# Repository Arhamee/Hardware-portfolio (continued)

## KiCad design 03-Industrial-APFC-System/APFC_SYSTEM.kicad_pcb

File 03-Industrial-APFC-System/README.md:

# Industrial Automatic Power Factor Correction System

Single-phase APFC system for loads up to 5kW, designed for real industrial
deployment in a DIN rail enclosure.

**Status:** In progress · 4-layer layout · to be open-sourced on OSHWLab
(OSHWLab Stars 2026)

## The Problem
Inductive loads — motors, compressors, welding machines — draw reactive current
that inflates bills and stresses wiring without doing useful work. Most affordable
solutions only *monitor*. This one corrects.

## Hardware
| Block | Part / Approach |
|---|---|
| MCU | ESP32-WROOM-32E (dual core, WiFi) |
| Voltage sensing | Isolated, via potential transformer |
| Current sensing | SCT-013 split-core CT (galvanic isolation) |
| Capacitor bank | Binary-weighted 60/120/240µF CBB65 — 7 steps, 1–7 kVAR |
| Switching | S216S02 solid state relays, zero-cross |
| Protection | MOV surge clamping · DIN rail EMI filter · fused mains · TVS |
| Display | SH1106 OLED |

## PCB
4-layer mixed-signal design:
- Mains-side isolated on bottom layer
- Analog sensing shielded by ground plane
- DIN rail form factor for direct panel installation

## Firmware / Dashboard
Live WiFi dashboard (no internet required) reporting Vrms, Irms, active/reactive/
apparent power, power factor, and capacitor bank status.

## Prior Version
Started as a Veroboard build with an Arduino Nano — calibrated sensors,
relay-switched capacitor bank, hysteresis-based correction algorithm.

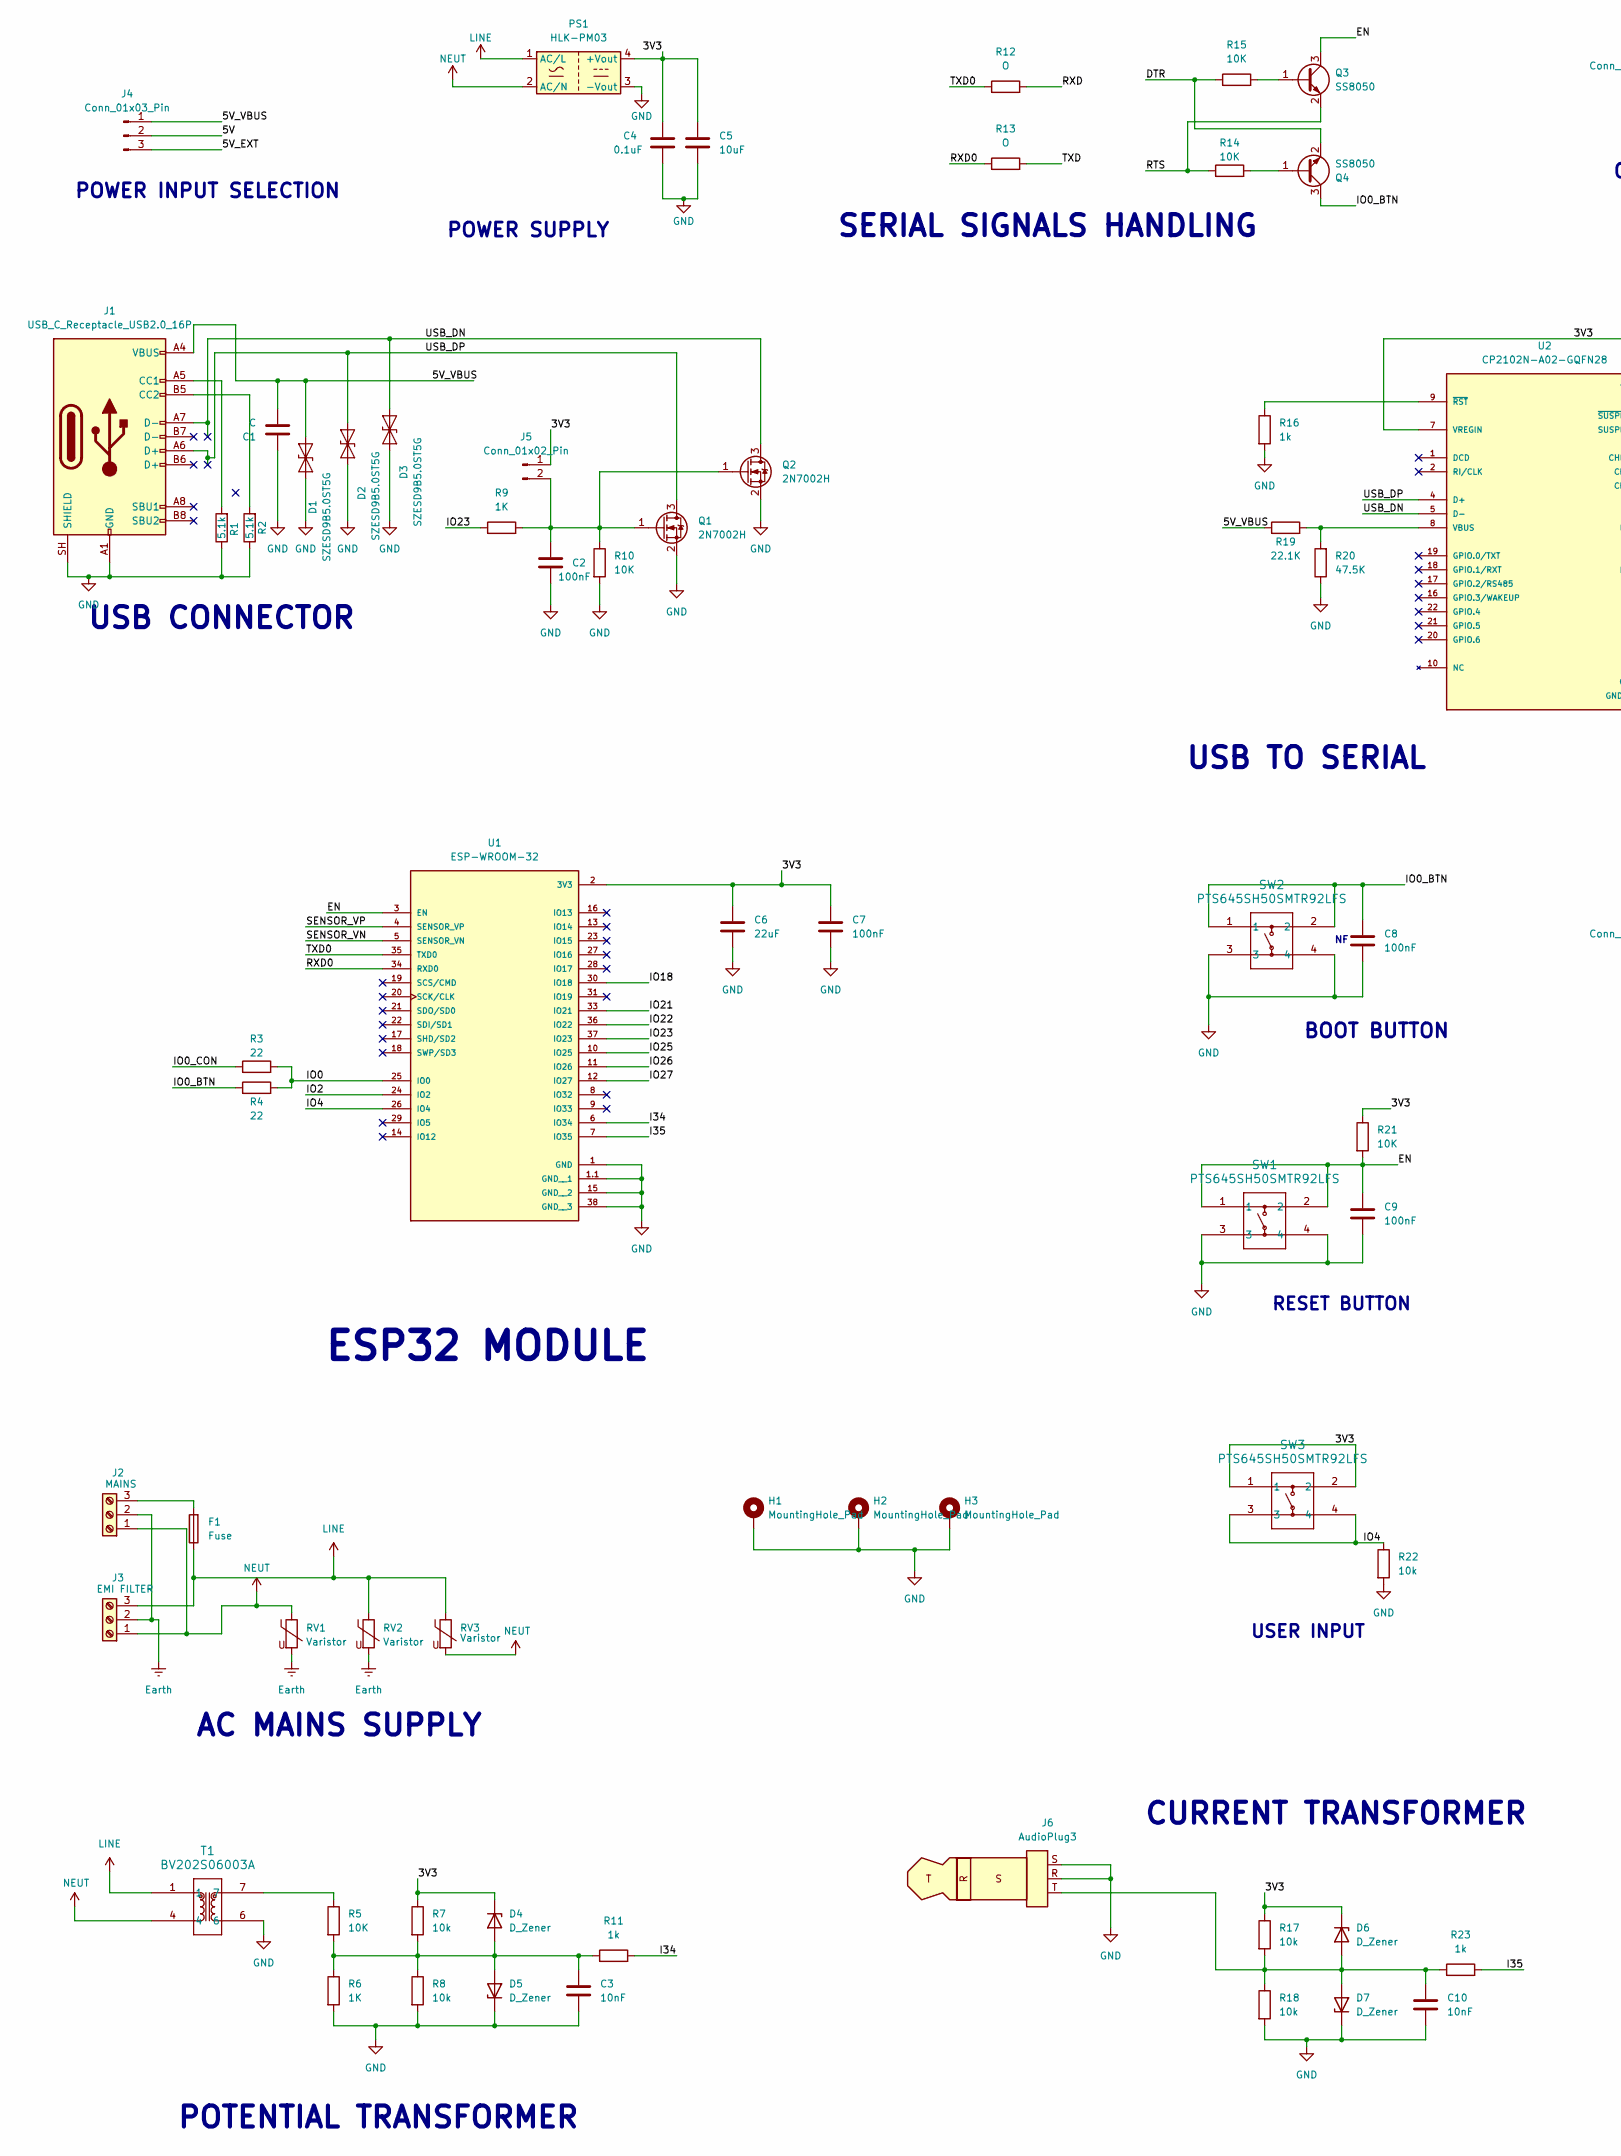
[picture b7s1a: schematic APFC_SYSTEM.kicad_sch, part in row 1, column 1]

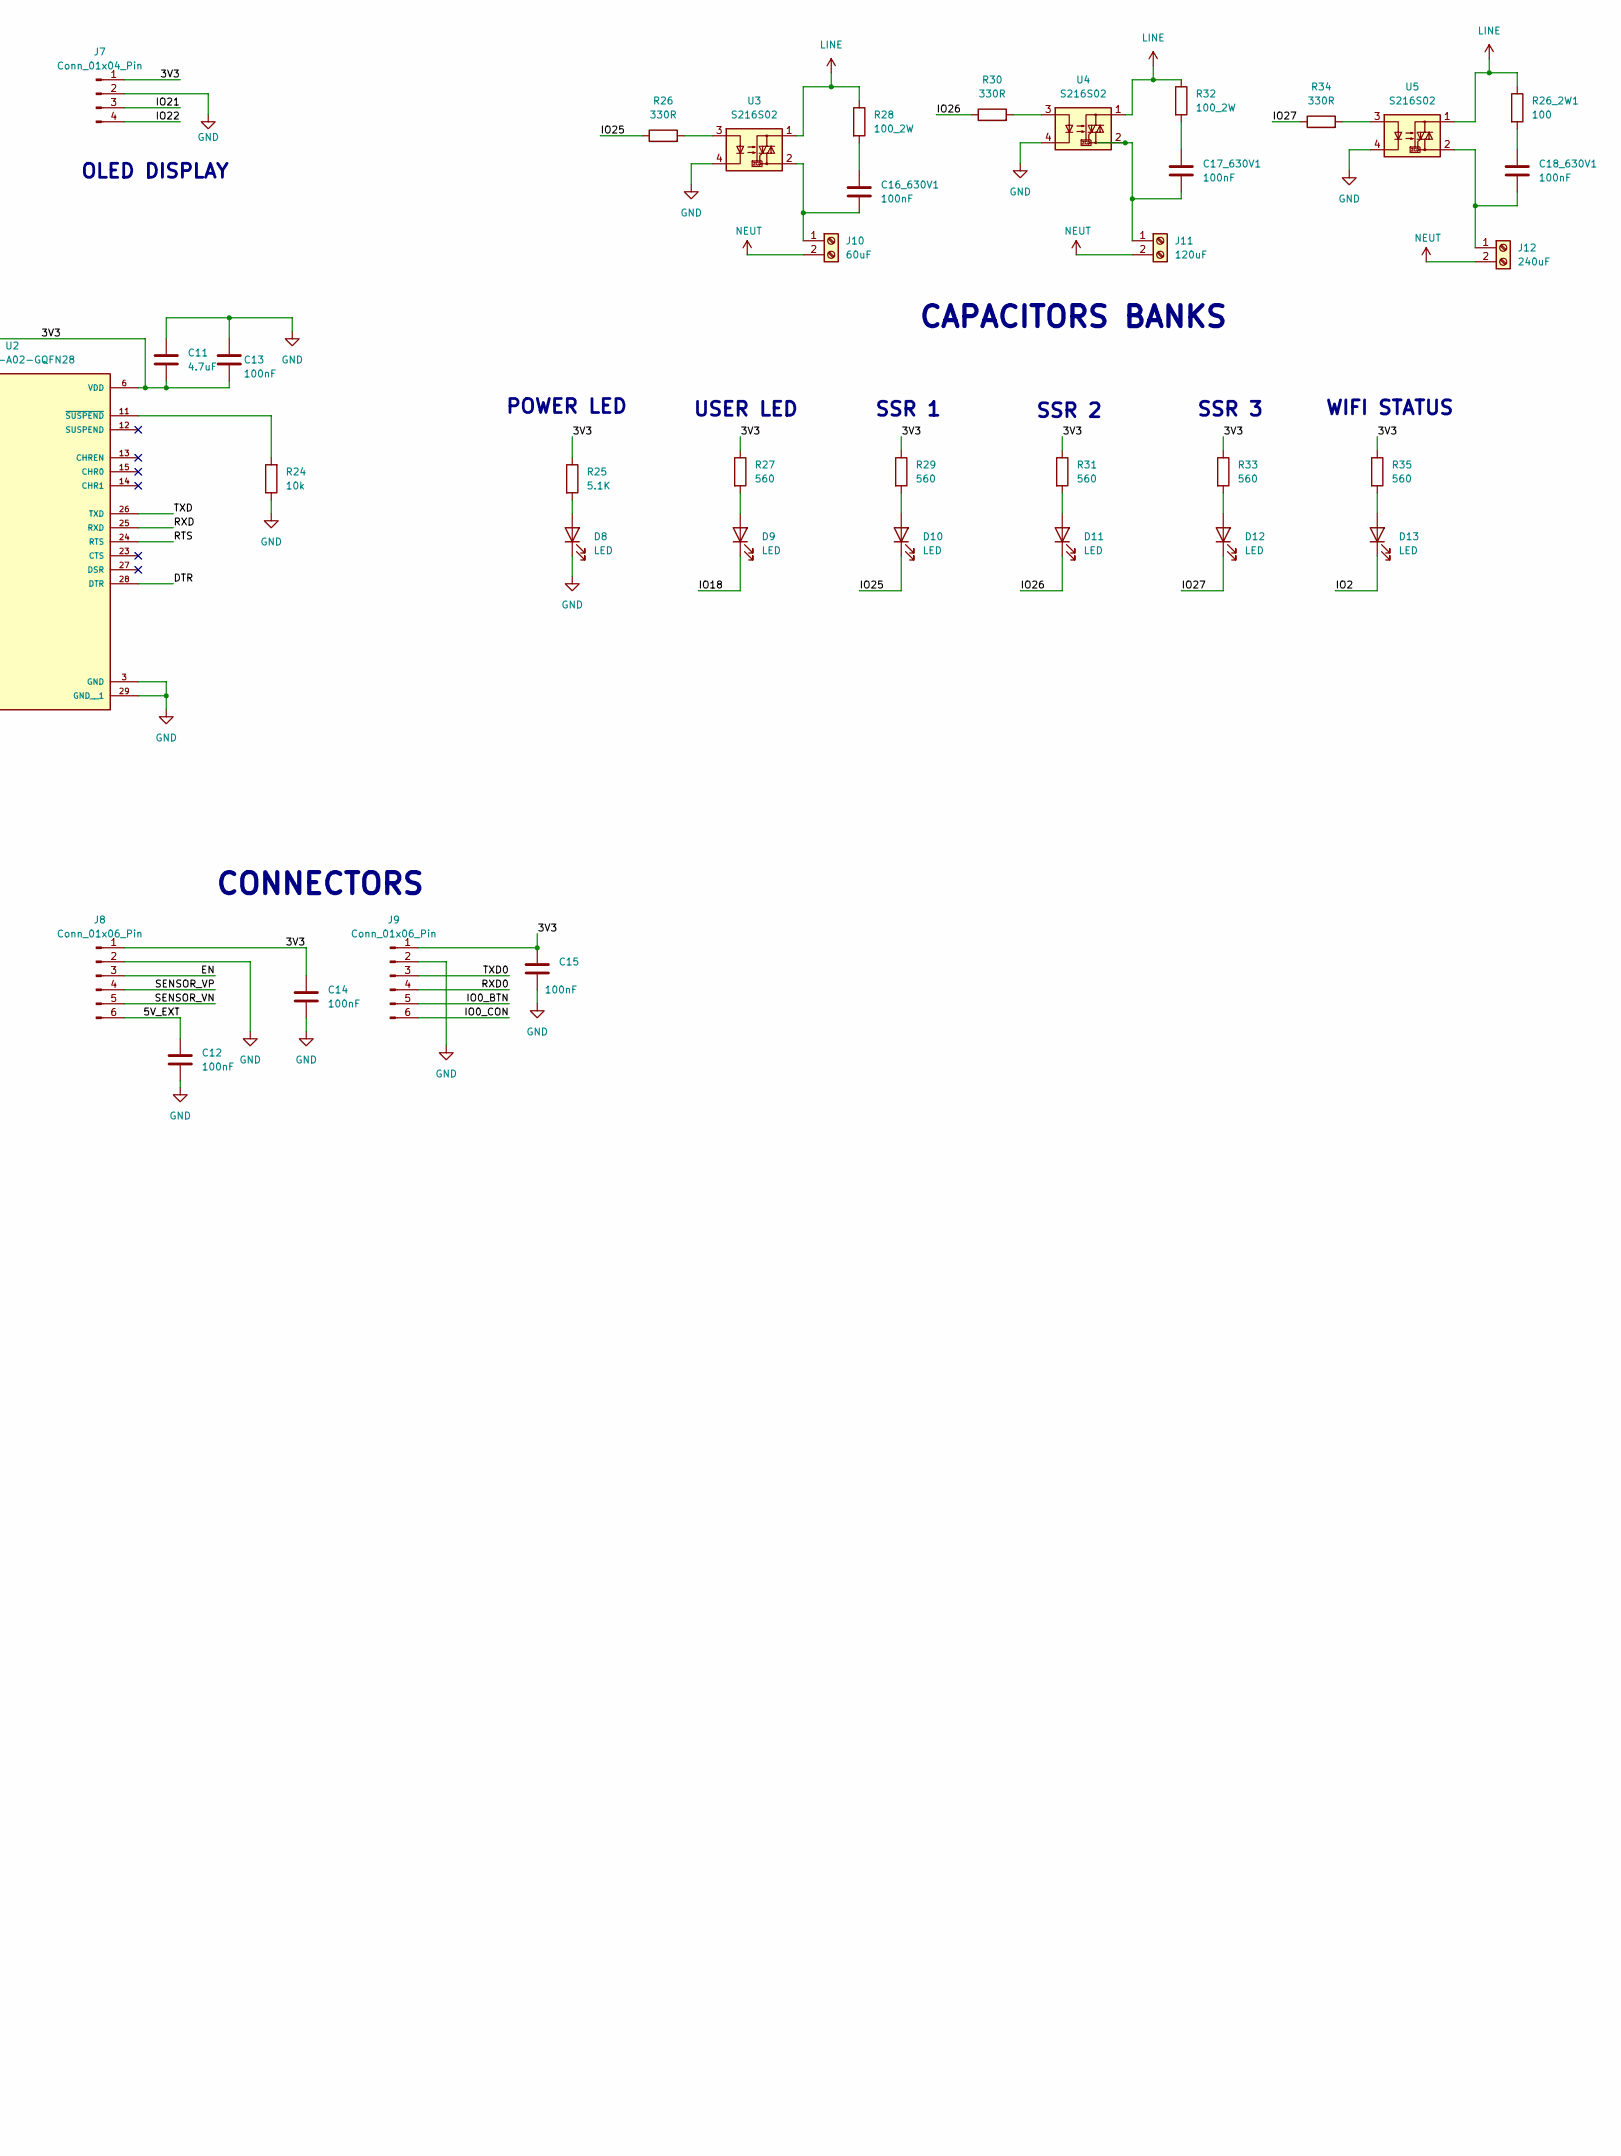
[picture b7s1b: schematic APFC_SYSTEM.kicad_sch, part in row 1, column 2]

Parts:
C1: C; C_0603_1608Metric_Pad1.08x0.95mm_HandSolder
C2, C7, C8, C9, C12, C13, C14, C15: 100nF; C_0603_1608Metric_Pad1.08x0.95mm_HandSolder
C3, C10: 10nF; C_0603_1608Metric_Pad1.08x0.95mm_HandSolder
C4: 0.1uF; C_0603_1608Metric_Pad1.08x0.95mm_HandSolder
C5: 10uF; C_0805_2012Metric_Pad1.18x1.45mm_HandSolder
C6: 22uF; C_0805_2012Metric_Pad1.18x1.45mm_HandSolder
C11: 4.7uF; C_0805_2012Metric_Pad1.18x1.45mm_HandSolder
C16_630V1, C17_630V1, C18_630V1: 100nF; C_Disc_D7.5mm_W5.0mm_P10.00mm
D1, D2, D3: SZESD9B5.0ST5G; D_SOD-923
D4, D5, D6, D7: D_Zener; D_0805_2012Metric_Pad1.15x1.40mm_HandSolder
D8, D9, D10, D11, D12, D13: LED; LED_0603_1608Metric_Pad1.05x0.95mm_HandSolder
F1: Fuse; FUSE_696105003002
H1, H2, H3: MountingHole_Pad; MountingHole_4.3mm_M4_DIN965_Pad
J1: USB_C_Receptacle_USB2.0_16P; USB_C_Receptacle_GCT_USB4105-xx-A_16P_TopMnt_Horizontal
J2: MAINS; TerminalBlock_Ningbo-Kagnex_HB9500M_1x03_P9.5mm
J3: EMI FILTER; TerminalBlock_Ningbo-Kagnex_HB9500M_1x03_P9.5mm
J4: Conn_01x03_Pin; PinHeader_1x03_P2.00mm_Vertical
J5: Conn_01x02_Pin; PinHeader_1x02_P1.27mm_Vertical
J6: AudioPlug3; Jack_3.5mm_CUI_SJ-3523-SMT_Horizontal
J7: Conn_01x04_Pin; PinHeader_1x04_P2.54mm_Vertical
J8, J9: Conn_01x06_Pin; PinHeader_1x06_P2.00mm_Vertical
J10: 60uF; TerminalBlock_Ningbo-Kagnex_HB9500M_1x02_P9.5mm
J11: 120uF; TerminalBlock_Ningbo-Kagnex_HB9500M_1x02_P9.5mm
J12: 240uF; TerminalBlock_Ningbo-Kagnex_HB9500M_1x02_P9.5mm
PS1: HLK-PM03; Converter_ACDC_Hi-Link_HLK-PMxx
Q1, Q2: 2N7002H; SOT-23
Q3, Q4: SS8050; SOT-23
R1, R2: 5.1k; R_0603_1608Metric_Pad0.98x0.95mm_HandSolder
R3, R4: 22; R_0402_1005Metric_Pad0.72x0.64mm_HandSolder
R5, R10, R14, R15: 10K; R_0603_1608Metric_Pad0.98x0.95mm_HandSolder
R6, R9: 1K; R_0603_1608Metric_Pad0.98x0.95mm_HandSolder
R7, R8, R17, R18, R22: 10k; R_0603_1608Metric_Pad0.98x0.95mm_HandSolder
R11, R23: 1k; R_0603_1608Metric_Pad0.98x0.95mm_HandSolder
R12, R13: O; R_0603_1608Metric_Pad0.98x0.95mm_HandSolder
R16: 1k; R_0402_1005Metric_Pad0.72x0.64mm_HandSolder
R19: 22.1K; R_0402_1005Metric_Pad0.72x0.64mm_HandSolder
R20: 47.5K; R_0402_1005Metric_Pad0.72x0.64mm_HandSolder
R21: 10K; R_0402_1005Metric_Pad0.72x0.64mm_HandSolder
R24: 10k; R_0402_1005Metric_Pad0.72x0.64mm_HandSolder
R25: 5.1K; R_0402_1005Metric_Pad0.72x0.64mm_HandSolder
R26, R30, R34: 330R; R_0603_1608Metric_Pad0.98x0.95mm_HandSolder
R26_2W1: 100; R_Axial_DIN0309_L9.0mm_D3.2mm_P15.24mm_Horizontal
R27: 560; R_0402_1005Metric_Pad0.72x0.64mm_HandSolder
R28, R32: 100_2W; R_Axial_DIN0309_L9.0mm_D3.2mm_P15.24mm_Horizontal
R29, R31, R33, R35: 560; R_0603_1608Metric_Pad0.98x0.95mm_HandSolder
RV1, RV2, RV3: Varistor; RV_Disc_D15.5mm_W3.9mm_P7.5mm
SW1, SW2, SW3: PTS645SH50SMTR92LFS; PTS645S_SMTR92_CNK
T1: BV202S06003A; VOLTAGE_TRANSFORMER
U1: ESP-WROOM-32; MODULE_ESP-WROOM-32
U2: CP2102N-A02-GQFN28; QFN50P500X500X80-29N; PARTREV 1.5
U3, U4, U5: S216S02; SIP4_Sharp-SSR_P7.62mm_Straight

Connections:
/3V3: C4.1, C5.1, C6.1, C7.1, C11.2, C13.2, C14.1, C15.1, D4.1 (K), D6.1 (K), J5.1, J7.1, J8.1, J9.1, PS1.4 (+Vout), R7.1, R17.1, R21.1, R25.1, R27.1, R29.1, R31.1, R33.1, R35.1, SW3.1, SW3.2, U1.2 (3V3), U2.6 (VDD), U2.7 (VREGIN)
/5V: J4.2
/5V_EXT: C12.1, J4.3, J8.6
/5V_VBUS: C1.2, D1.2 (A2), J1.A4 (VBUS), J1.A9 (VBUS), J1.B4 (VBUS), J1.B9 (VBUS), J4.1, R19.1
/DTR: Q4.2 (E), R15.1, U2.28 (DTR)
/EN: C9.1, J8.3, Q3.3 (C), R21.2, SW1.1, SW1.2, U1.3 (EN)
/I34: R11.2, U1.6 (IO34)
/I35: R23.2, U1.7 (IO35)
/IO0: R3.2, R4.2, U1.25 (IO0)
/IO0_BTN: C8.1, J9.5, Q4.3 (C), R4.1, SW2.1, SW2.2
/IO0_CON: J9.6, R3.1
/IO2: D13.1 (K), U1.24 (IO2)
/IO4: R22.1, SW3.3, SW3.4, U1.26 (IO4)
/IO18: D9.1 (K), U1.30 (IO18)
/IO21: J7.3, U1.33 (IO21)
/IO22: J7.4, U1.36 (IO22)
/IO23: R9.1, U1.37 (IO23)
/IO25: D10.1 (K), R26.1, U1.10 (IO25)
/IO26: D11.1 (K), R30.1, U1.11 (IO26)
/IO27: D12.1 (K), R34.1, U1.12 (IO27)
/RTS: Q3.2 (E), R14.1, U2.24 (RTS)
/RXD: R12.2, U2.25 (RXD)
/RXD0: J9.4, R13.1, U1.34 (RXD0)
/SENSOR_VN: J8.5, U1.5 (SENSOR_VN)
/SENSOR_VP: J8.4, U1.4 (SENSOR_VP)
/TXD: R13.2, U2.26 (TXD)
/TXD0: J9.3, R12.1, U1.35 (TXD0)
/USB_DN: D3.2 (A2), J1.A7 (D-), Q2.3 (D), U2.5 (D-)
/USB_DP: D2.2 (A2), J1.A6 (D+), Q1.3 (D), U2.4 (D+)
Earth: J2.2, J3.2, RV1.2, RV2.2
GND: C1.1, C2.2, C3.2, C4.2, C5.2, C6.2, C7.2, C8.2, C9.2, C10.2, C11.1, C12.2, C13.1, C14.2, C15.2, D1.1 (A1), D2.1 (A1), D3.1 (A1), D5.1 (K), D7.1 (K), D8.1 (K), H1.1 (1_1), H2.1 (1_1), H3.1 (1_1), J1.A1 (GND), J1.A12 (GND), J1.B1 (GND), J1.B12 (GND), J1.SH (SHIELD), J6.R, J6.S, J7.2, J8.2, J9.2, PS1.3 (-Vout), Q1.2 (S), Q2.2 (S), R1.1, R2.1, R6.2, R8.2, R10.2, R16.2, R18.2, R20.1, R22.2, R24.1, SW1.3, SW1.4, SW2.3, SW2.4, T1.6, U1.1 (GND), U1.1.1 (GND__1), U1.15 (GND__2), U1.38 (GND__3), U2.3 (GND), U2.29 (GND__1), U3.4, U4.4, U5.4
LINE: F1.1, J3.3, PS1.1 (AC/L), R26_2W1.1, R28.1, R32.1, RV2.1, RV3.1, T1.1, U3.1, U4.1, U5.1
NEUT: J2.1, J3.1, J10.2, J11.2, J12.2, PS1.2 (AC/N), RV1.1, RV3.2, T1.4
unnamed: C16_630V1.1, R28.2
unnamed: C17_630V1.1, R32.2
unnamed: C18_630V1.1, R26_2W1.2
unnamed: C3.1, D4.2 (A), D5.2 (A), R5.2, R6.1, R7.2, R8.1, R11.1
unnamed: C10.1, D6.2 (A), D7.2 (A), J6.T, R17.2, R18.1, R23.1
unnamed: D8.2 (A), R25.2
unnamed: D9.2 (A), R27.2
unnamed: D10.2 (A), R29.2
unnamed: D11.2 (A), R31.2
unnamed: D12.2 (A), R33.2
unnamed: D13.2 (A), R35.2
unnamed: J1.A5 (CC1), R1.2
unnamed: J1.B5 (CC2), R2.2
unnamed: F1.2, J2.3
unnamed: C2.1, J5.2, Q1.1 (G), Q2.1 (G), R9.2, R10.1
unnamed: C16_630V1.2, J10.1, U3.2
unnamed: C17_630V1.2, J11.1, U4.2
unnamed: C18_630V1.2, J12.1, U5.2
unnamed: Q3.1 (B), R15.2
unnamed: Q4.1 (B), R14.2
unnamed: R5.1, T1.7
unnamed: R26.2, U3.3
unnamed: R30.2, U4.3
unnamed: R34.2, U5.3
unnamed: R19.2, R20.2, U2.8 (VBUS)
unnamed: R16.1, U2.9 (~RST)
unnamed: R24.2, U2.11 (~SUSPEND)

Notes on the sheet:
CURRENT TRANSFORMER
CAPACITORS BANKS
WIFI STATUS
SERIAL SIGNALS HANDLING
SSR 1
POWER LED
POTENTIAL TRANSFORMER
POWER INPUT SELECTION
USB CONNECTOR
USER LED
CONNECTORS
SSR 2
AC MAINS SUPPLY
BOOT BUTTON
USB TO SERIAL
OLED DISPLAY
RESET BUTTON
ESP32 MODULE
SSR 3
USER INPUT
POWER SUPPLY

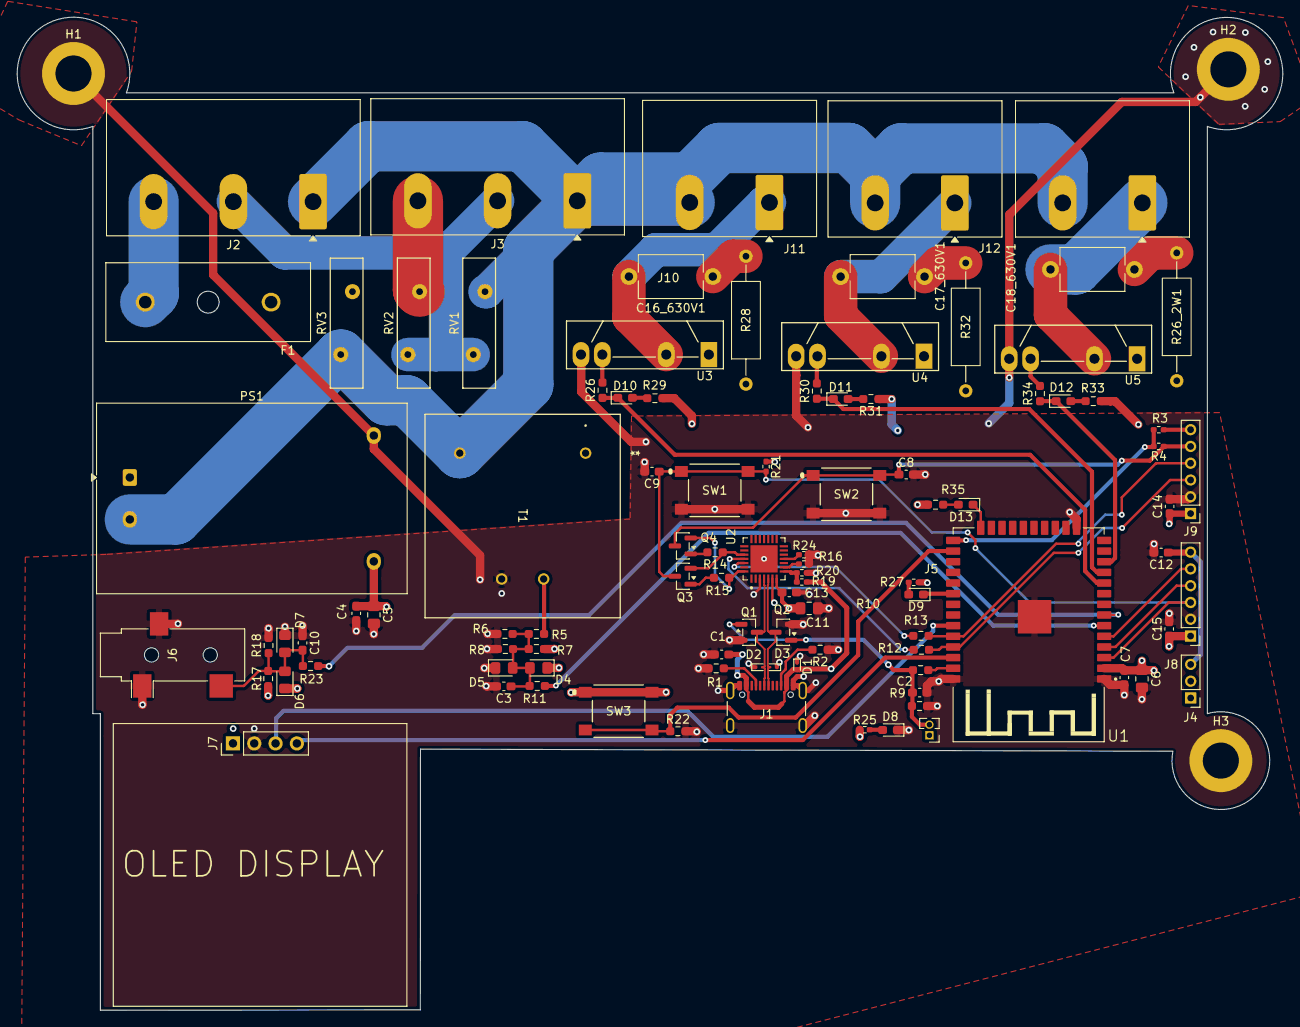
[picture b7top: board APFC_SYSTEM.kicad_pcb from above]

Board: 4 copper layers, 150.9 x 118.4 mm, 100 parts (0 on the bottom side), 59 nets.

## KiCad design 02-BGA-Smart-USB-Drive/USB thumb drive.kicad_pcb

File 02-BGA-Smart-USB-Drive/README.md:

# Smart USB Thumb Drive — RP2040 + eMMC

4-layer board packing an RP2040, USB2244 bridge, and 64GB eMMC in a
153-ball 0.5mm-pitch BGA into a thumb-drive footprint.

**Status:** Design complete · DRC-clean · manufacturing-ready · not yet fabricated

## Specs
| | |
|---|---|
| Layers | 4 |
| MCU | RP2040 |
| Bridge | USB2244 |
| Storage | 64GB eMMC — 153-ball BGA, 0.5mm pitch |
| Power path | LM66100 dual ideal-diode OR-ing |

## Design Challenges
- **Fine-pitch BGA escape** — via-in-pad and dogbone fanout strategies; took
  several iterations before clearances resolved cleanly
- **90Ω USB 2.0 differential pair** — held by planning the stackup deliberately
  rather than accepting defaults
- **eMMC parallel bus length-matching** — tighter tolerances than any previous design
- **Dual-port power** — two independent USB ports sharing power duty without backfeeding
- **Documented design intent** — scoped DRC exceptions rather than blanket
  rule suppression

## Background
Built following Peter Dalmaris's *KiCad Advanced: Design a Smart USB Thumb Drive* (26 hrs).

If you've routed fine-pitch BGAs and something here looks wrong — open an Issue.
I'd rather be corrected now than after boards come back from fab.

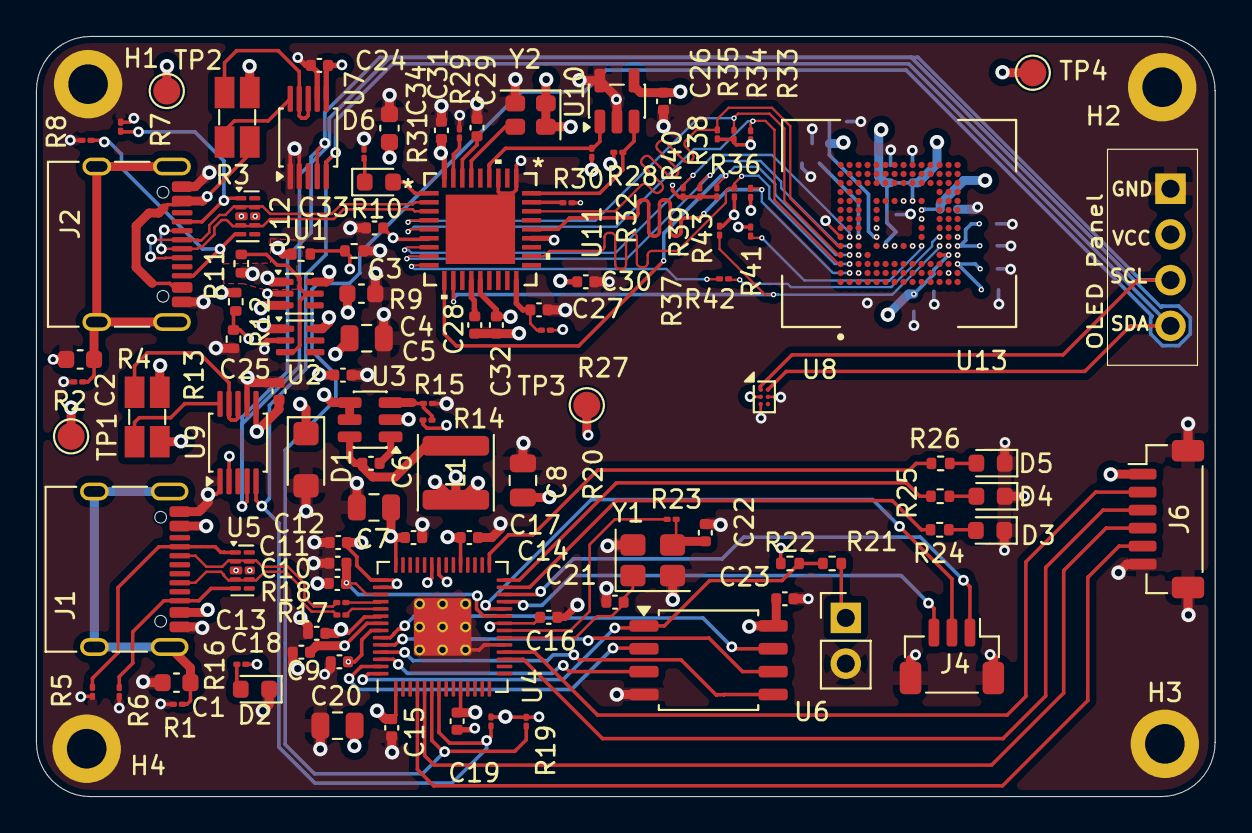
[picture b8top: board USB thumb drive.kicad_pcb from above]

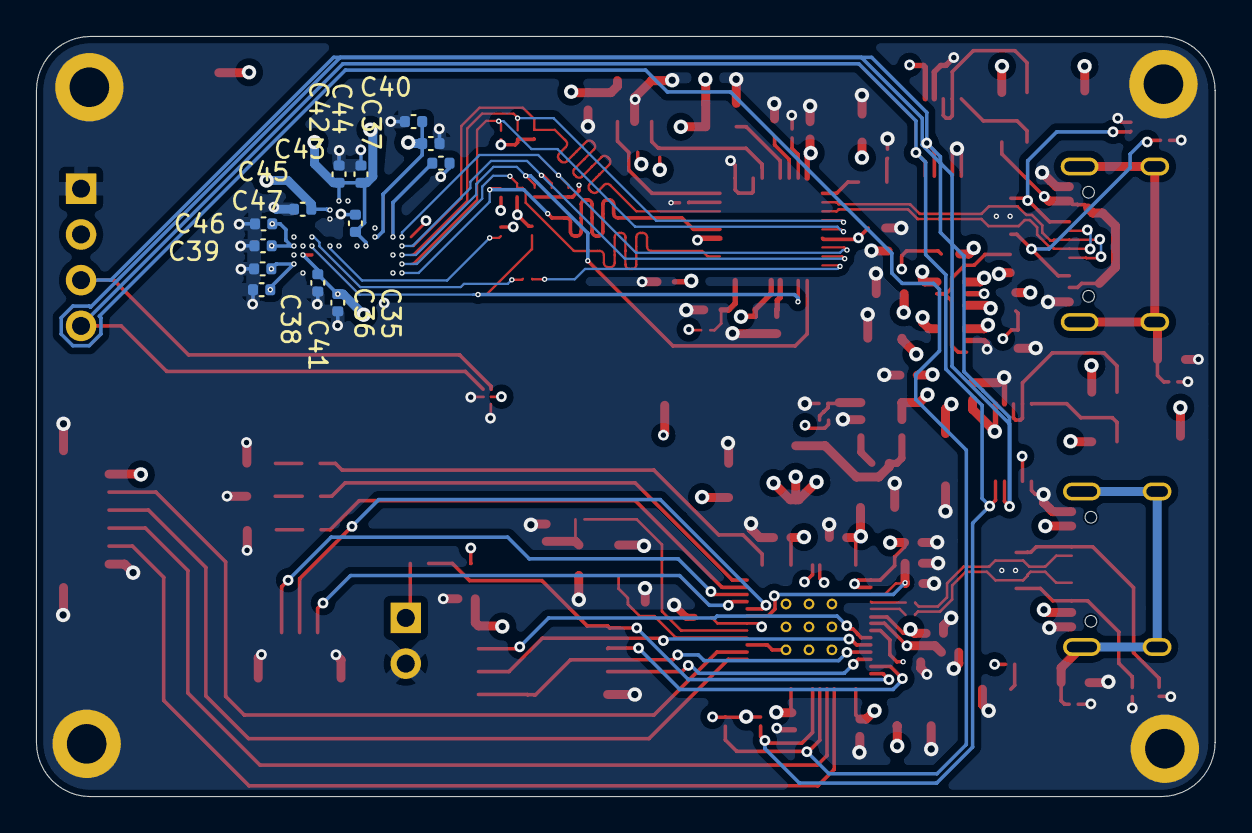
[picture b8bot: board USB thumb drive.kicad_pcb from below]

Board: 4 copper layers, 65.5 x 42.2 mm, 126 parts (13 on the bottom side), 78 nets.

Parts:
C1, C2: 2.2n 100V; C_0603_1608Metric
C3: 1uF; C_0603_1608Metric
C4, C27, C30, C31, C32, C33, C35, C42, C43, C44, C45: 0.1u 10V; C_0402_1005Metric
C5, C7, C8: 22u 10V; C_0805_2012Metric
C6, C28, C29, C36, C46: 1u 10V; C_0402_1005Metric
C9, C10, C12, C14, C15, C16, C17, C18, C19, C23: 1n / 10V; C_0402_1005Metric
C11, C13: 1u /10V; C_0402_1005Metric
C20: 10u/10V; C_0805_2012Metric
C21, C22: 15p 10V; C_0402_1005Metric
C24, C25: 1u/10V; C_0402_1005Metric
C26: 100n 10V; C_0402_1005Metric
C34: 4.7u 10V; C_0603_1608Metric
C37, C38, C39, C40, C41, C47: 2.2u 10V; C_0402_1005Metric
D1: SMF5V0A; D_SMF
D2: LED RED; LED_0603_1608Metric
D3, D4, D5, D6: LED; LED_0603_1608Metric
DS1: OLED_SSD1306_0p91_128x32_I2C; SSD1306-0.91-OLED-4pin-128x32
H1, H2, H3, H4: MountingHole_Pad; MountingHole_2.2mm_M2_DIN965_Pad
J1, J2: USB_C_Receptacle_USB2.0_16P; USB_C_Receptacle_XKB_U262-16XN-4BVC11
J3: Conn_01x02; PinHeader_1x02_P2.54mm_Vertical
J4: Conn_01x03_MountingPin; JST_SH_BM03B-SRSS-TB_1x03-1MP_P1.00mm_Vertical
J6: Conn_01x06_MountingPin; JST_SH_BM06B-SRSS-TB_1x06-1MP_P1.00mm_Vertical
L1: 2.2uH/4,3A; L_Sunlord_SWPA4020S
R1, R2: 1M/1%; R_01005_0402Metric
R3, R4: 2m/1%; R_Shunt_Ohmite_LVK12
R5, R6, R7, R8: 5.5K /1%; R_01005_0402Metric
R9, R11, R13: 100K; R_0402_1005Metric
R10, R12: 150K; R_0402_1005Metric
R14: 100K/1%; R_01005_0402Metric
R15: 22.1K/1%; R_01005_0402Metric
R16, R23: 1K/1%; R_01005_0402Metric
R17, R18: 27.4/1%; R_01005_0402Metric
R19, R20: 4.7K/1%; R_01005_0402Metric
R21, R24, R25, R26: 1k; R_0402_1005Metric
R22: DNF; R_0402_1005Metric
R27, R28, R30, R41, R43: 10K/1%; R_01005_0402Metric
R29: 12K /1%; R_01005_0402Metric
R31: 330/1%; R_01005_0402Metric
R32: 10K /1%; R_01005_0402Metric
R33, R34, R35, R36, R37, R38, R39, R40: 47K/1%; R_01005_0402Metric
R42: 22/1%; R_01005_0402Metric
TP1, TP2, TP3, TP4: TestPoint; TestPoint_Pad_D1.5mm
U1, U2: LM66100DCK; SOT-363_SC-70-6
U3: SY8253ADC; TSOT-23-6
U4: RP2040; RP2040-QFN-56
U5, U12: D3V3XA4B10LP; Diodes_UDFN-10_1x2.5mm_P0.5mm
U6: W25Q128JVS; SOIC-8_5.3x5.3mm_P1.27mm
U7, U9: INA226; TSSOP-10_3x3mm_P0.5mm
U8: TMP119AIYBGR; Texas_DSBGA-6_0.95x1.488mm_Layout2x3_P0.4mm
U10: AT24CS04-STUM; SOT-23-5
U11: USB2244-AEZG-06; QFN36_6X6MC_MCH
U13: MTFC64GAPALBH-IT; BGA153N50P14X14_1300X1150X110N
Y1: Crystal_GND24; Crystal_SMD_3225-4Pin_3.2x2.5mm
Y2: SG-210STF; Oscillator_SMD_SeikoEpson_SG210-4Pin_2.5x2.0mm

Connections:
+1V1: C9.1, C10.1, C11.1, U4.23 (DVDD), U4.45 (VREG_VOUT), U4.50 (DVDD)
+3V3: C7.1, C8.1, C12.1, C13.1, C14.1, C15.1, C16.1, C17.1, C18.1, C19.1, C20.1, C23.1, C24.1, C25.1, C26.1, C30.2, C31.2, C32.2, C33.2, C34.2, C35.2, C36.2, C37.2, C38.2, C39.2, C40.2, C41.2, C42.2, C43.2, C44.2, C45.2, C46.2, C47.2, DS1.2 (VCC), J6.1, L1.2, R14.1, R16.1, R19.2, R20.2, R22.1, R27.1, R28.1, R30.1, R33.1, R34.1, R35.1, R36.1, R37.1, R38.1, R39.1, R40.1, R41.2, R43.1, TP3.1 (1_1), TP4.1 (1_1), U4.1 (IOVDD), U4.10 (IOVDD), U4.22 (IOVDD), U4.33 (IOVDD), U4.42 (IOVDD), U4.43 (ADC_AVDD), U4.44 (VREG_IN), U4.48 (USB_VDD), U4.49 (IOVDD), U6.8 (VCC), U7.6 (VS), U8.B1 (V+), U9.2 (A0), U9.6 (VS), U10.4 (VCC), U11.6 (VDD33), U11.14 (VDD33), U11.22 (VDD33), U11.36 (VDDA33), U13.C2 (VDDIM), U13.C6 (VCCQ), U13.E6 (VCC), U13.F5 (VCC__1), U13.J10 (VCC__2), U13.K9 (VCC__3), U13.M4 (VCCQ__1), U13.N4 (VCCQ__2), U13.P3 (VCCQ__3), U13.P5 (VCCQ__4), Y2.1 (~ST), Y2.4 (Vcc)
/ORING_POWER/NOTIFY_3V3_CON1: R9.2, R10.1, U4.36 (GPIO24)
/ORING_POWER/NOTIFY_3V3_CON2: R11.2, R12.1, U4.37 (GPIO25)
/ORING_POWER/ORING_5V: C3.1, C4.1, C5.1, D1.1 (A1), U1.6 (VOUT), U2.6 (VOUT), U3.4 (EN), U3.5 (VIN)
/RP2041/GPIO14: J6.3, U4.17 (GPIO14)
/RP2041/GPIO15: J6.2, U4.18 (GPIO15)
/RP2041/I2C0_SCL: DS1.4 (SDA), R20.1, U4.7 (GPIO5), U7.5 (SCL), U8.A2 (SCL), U9.5 (SCL)
/RP2041/I2C0_SDA: DS1.3 (SCL), R19.1, U4.6 (GPIO4), U7.4 (SDA), U8.A1 (SDA), U9.4 (SDA)
/RP2041/I2C_SCL: J6.4, U4.5 (GPIO3)
/RP2041/I2C_SDA: J6.5, U4.4 (GPIO2)
/RP2041/LED_A: R24.2, U4.27 (GPIO16)
/RP2041/LED_B: R25.2, U4.28 (GPIO17)
/RP2041/LED_C: R26.2, U4.29 (GPIO18)
/RP2041/QSPI_SCLK: U4.52 (QSPI_SCLK), U6.6 (CLK)
/RP2041/QSPI_SD0: U4.53 (QSPI_SD0), U6.5 (DI/IO_{0})
/RP2041/QSPI_SD1: U4.55 (QSPI_SD1), U6.2 (DO/IO_{1})
/RP2041/QSPI_SD2: U4.54 (QSPI_SD2), U6.3 (~WP/IO_{2})
/RP2041/QSPI_SD3: U4.51 (QSPI_SD3), U6.7 (~HOLD/~RESET/IO_{3})
/RP2041/QSPI_SS: R21.1, R22.2, U4.56 (QSPI_SS), U6.1 (~CS)
/RP2041/RP_USB_D+: J1.B6 (D+), R17.2, U5.4, U5.7 (NC)
/RP2041/RP_USB_D-: J1.B7 (D-), R18.2, U5.2
/RP2041/RP_XIN: C21.1, U4.20 (XIN), Y1.1
/RP2041/RP_XOUT: R23.2, U4.21 (XOUT)
/RP2041/RUN: J4.1, U4.26 (RUN)
/RP2041/SWCLK: J4.2, U4.24 (SWCLK)
/RP2041/SWD: J4.3, U4.25 (SWD)
/RP2041/~USB_BOOT: J3.1, R21.2
/USB_BRIDGE1/MMCD0: R33.2, U11.5 (SD_D0), U13.A3 (DAT0)
/USB_BRIDGE1/MMCD1: R34.2, U11.4 (SD_D1), U13.A4 (DAT1)
/USB_BRIDGE1/MMCD2: R35.2, U11.25 (SD_D2), U13.A5 (DAT2)
/USB_BRIDGE1/MMCD3: R36.2, U11.23 (SD_D3), U13.B2 (DAT3)
/USB_BRIDGE1/MMCD4: R37.2, U11.20 (SD_D4), U13.B3 (DAT4)
/USB_BRIDGE1/MMCD5: R38.2, U11.10 (SD_D5), U13.B4 (DAT5)
/USB_BRIDGE1/MMCD6: R39.2, U11.8 (SD_D6), U13.B5 (DAT6)
/USB_BRIDGE1/MMCD7: R40.2, U11.7 (SD_D7), U13.B6 (DAT7)
/USB_BRIDGE1/MMC_CLK: R42.2, U11.9 (SD_CLK)
/USB_BRIDGE1/SCL_USB2244: R30.2, U10.1 (SCL), U11.31 (TXD/SCK)
/USB_BRIDGE1/SDA_USB2244: R28.2, U10.3 (SDA), U11.27 (RXD/SDA)
/USB_BRIDGE1/STORAGE_USB+: J2.A6 (D+), J2.B6 (D+), U11.2 (USB+), U12.2, U12.9 (NC)
/USB_BRIDGE1/STORAGE_USB-: J2.A7 (D-), J2.B7 (D-), U11.3 (USB-), U12.4, U12.7 (NC)
/USB_CC1_CON1: J2.A5 (CC1), R7.2, U12.1
/USB_CC1_CON2: J1.A5 (CC1), R5.2, U5.1
/USB_CC2_CON1: J2.B5 (CC2), R8.1, U12.5
/USB_CC2_CON2: J1.B5 (CC2), R6.1, U5.5
/VBUS_MCU: R4.4, R11.1, TP1.1 (1_1), U1.3 (~CE), U2.1 (VIN)
/VBUS_MCU_IN+: R4.2, U9.10 (Vin+)
/VBUS_MCU_IN-: R4.3, U9.8 (Vbus), U9.9 (Vin-)
/VBUS_STORAGE: R3.4, R9.1, R13.1, TP2.1 (1_1), U1.1 (VIN)
/VBUS_STORAGE_IN+: R3.2, U7.10 (Vin+)
/VBUS_STORAGE_IN-: R3.3, U7.8 (Vbus), U7.9 (Vin-)
/eMMC_STORAGE1/MMC_CLK_L: R42.1, U13.M6 (CLK)
/eMMC_STORAGE1/MMC_CMD_L: R43.2, U11.11 (SD_CMD), U13.M5 (CMD)
GND: C1.2, C2.2, C3.2, C4.2, C5.2, C7.2, C8.2, C9.2, C10.2, C11.2, C12.2, C13.2, C14.2, C15.2, C16.2, C17.2, C18.2, C19.2, C20.2, C21.2, C22.2, C23.2, C24.2, C25.2, C26.2, C27.2, C28.1, C29.1, C30.1, C31.1, C32.1, C33.1, C34.1, C35.1, C36.1, C37.1, C38.1, C39.1, C40.1, C41.1, C42.1, C43.1, C44.1, C45.1, C46.1, C47.1, D1.2 (A2), D2.1 (K), D3.1 (K), D4.1 (K), D5.1 (K), DS1.1 (GND), H1.1 (1_1), H2.1 (1_1), H3.1 (1_1), H4.1 (1_1), J1.A1 (GND), J1.A12 (GND), J1.B1 (GND), J1.B12 (GND), J2.A1 (GND), J2.A12 (GND), J2.B1 (GND), J2.B12 (GND), J3.2, J4.MP (MountPin), J6.6, J6.MP (MountPin), R1.2, R2.2, R5.1, R6.2, R7.1, R8.2, R10.2, R12.2, R15.2, R29.2, R31.1, R32.1, U1.2 (GND), U2.2 (GND), U3.2 (GND), U4.19 (TESTEN), U4.57 (GND), U5.3 (VSS), U5.8 (VSS), U6.4 (GND), U7.1 (A1), U7.2 (A0), U7.7 (GND), U8.B2 (GND), U8.C1 (ADD0), U9.1 (A1), U9.7 (GND), U10.2 (GND), U10.5 (WP), U11.28 (TEST), U11.30 (SD_WP), U11.37 (EPAD), U12.3 (VSS), U12.8 (VSS), U13.A6 (VSS), U13.C4 (VSSQ), U13.E7 (VSS__1), U13.G5 (VSS__2), U13.H10 (VSS__3), U13.J5 (VSS__4), U13.K8 (VSS__5), U13.N2 (VSSQ__1), U13.N5 (VSSQ__2), U13.P4 (VSSQ__3), U13.P6 (VSSQ__4), Y1.2 (G), Y1.4 (G), Y2.2 (GND)
unnamed: C22.1, R23.1, Y1.3
unnamed: D2.2 (A), R16.2
unnamed: D3.2 (A), R24.1
unnamed: D4.2 (A), R25.1
unnamed: D5.2 (A), R26.1
unnamed: D6.2 (A), U11.1 (LED)
unnamed: D6.1 (K), R31.2
unnamed: C1.1, J1.SH (SHIELD), R1.1
unnamed: J1.A4 (VBUS), J1.A9 (VBUS), J1.B4 (VBUS), J1.B9 (VBUS), R4.1
unnamed: C2.1, J2.SH (SHIELD), R2.1
unnamed: J2.A4 (VBUS), J2.A9 (VBUS), J2.B4 (VBUS), J2.B9 (VBUS), R3.1
unnamed: R13.2, U1.5 (ST), U2.3 (~CE)
unnamed: C6.1, U3.1 (BOOST)
unnamed: R14.2, R15.1, U3.3 (FB)
unnamed: C6.2, L1.1, U3.6 (SW)
unnamed: R18.1, U4.46 (USB_DM)
unnamed: R17.1, U4.47 (USB_DP)
unnamed: R29.1, U11.35 (RBIAS)
unnamed: C27.1, R27.2, U11.18 (RESET_N)
unnamed: R32.2, U11.26 (SD_NCD)
unnamed: U11.33 (XTAL1(CLKIN)), Y2.3 (OUT)
unnamed: C28.2, U11.13 (VDD18)
unnamed: C29.2, U11.34 (VDD18PLL)
unnamed: R41.1, U13.K5 (RST_N)

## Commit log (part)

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2026-03-25 Revise README for hardware design portfolio
    Updated README to include project details and structure.
2026-03-25 ESP8266-Water-Controller
2026-03-25 NE555-Analog-Automation
2026-03-25 DeskBuddy-v2
2026-03-25 MSPM0-DevBoard
2026-03-25 ESP32-S3-IoT-Board
2026-03-25 STM32WB-4Layer-USB-RF
2026-03-25 ESP32-C3-IoT-DevBoard/
2026-03-25 ESP32-S3-ENS210-Sensor
2026-03-25 STM32-BlackPill
2026-03-25 AC-Energy-Analyzer
